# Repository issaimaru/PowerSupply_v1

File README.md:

# アズサ(Azusa)

<br>

<br>
この基板はJLCPCB様のFree PCB Sponsorshipにて制作しています．<br>

## Overview
  [MotorDriver-Controller_v4](https://github.com/TNCT-Mechatech/MotorDriver-Controller_v4)の機能+αと電源回路を合体させた統合型電源基板<br>
 
## Environments
&emsp;
&emsp;&emsp;
<br>

## Usage

1. [DriveUnit Bseries](https://github.com/Issaimaru/MoterDriver_v1)を使用したいチャネルのカードエッジコネクタに差し込む．<br>
1. モータードライバを差し込んだエッジコネクタと同じチャネルにモータを接続し，必要に応じて同じチャネルのコネクタにロータリーエンコーダを接続する．<br>
1. 非常停止スイッチを刺したコネクタの下にあるトグルスイッチをONに，それ以外のトグルスイッチをOFFにする．
1. XT90とUSB Type-Cからそれぞれ電源を供給し，非常停止スイッチをONにすると稼働する．
> **Note**<br>
> USB Type-C用電源を省略する方法はDescriptionsを参照<br>

## Features
<dl>
  <dt>通信プロトコル</dt>
  <dd>CAN with Flexible Data Rate(CAN FD)</dd>
  <dt>通信用コネクタ・ケーブル</dt>
  <dd>RJ-45/LANケーブル</dd>
  <dt>マイクロコンピュータ</dt>
  <dd>STM32F446RE</dd>
  <dt>特殊回路</dt>
  <dd>
  ・オートディスチャージ回路<br>
  ・車載用スローブローヒューズ

  <dt>保護回路(電源側)</dt>
  <dd>
  ・過電流保護(閾値可変)<br>
  ・ヒステリシス付き過熱保護<br>
  ・短絡保護<br>
  ・突入電流抑制<br>
  </dd>
  <dt>保護回路(信号側)</dt>
  <dd>
  ・過電圧保護<br>
  ・過電圧クランプ<br>
  ・突入電流抑制<br>
  ・過電流保護(東芝のeFuseを使用)<br>
  ・過熱保護<br>

## Descriptions
本ハードウェアの使用方法を詳しく書いていきます．<br>
質問や連絡等あれば[@TakenMaker](https://twitter.com/TakenMaker)までお願いします．<br>

### 回路図
&ensp;&ensp;

#### 始動方法
始動方法については[Usage](#usage)で示しました．<br>
ここでは始動時の応用的な使い方について紹介していきます．

- 信号用バッテリーの省略

<br>

JP6で信号用の電源をUSB給電or外部給電に切り替えることができます．<br>
外部電源としては，SPOWのピンに接続された電源かリポバッテリーか選ぶことができます．<br>
リポバッテリーの場合は「GND」と「SPOW」のピンヘッダを短絡してください．<br>
その際にE5VのLEDが点灯していることを確認してください．

## Bills of materials
> **Note**<br>
>最低限の部品のみここに書いています．<br>
>はんだ付けに必要な部品を調べるときは以下のexcelファイルを見るか，BOMファイルを出力してください．<br>
>[アズサ(Azusa)-ver2.0_必要部品.xlsx](src/%E3%82%A2%E3%82%BA%E3%82%B5(Azusa)-ver2.0_%E5%BF%85%E8%A6%81%E9%83%A8%E5%93%81.xlsx)
<br>
<dl>
  <dt>マイクロコンピュータ</dt>
  <dd>

  [STM32F446RET6](https://www.digikey.jp/ja/products/detail/stmicroelectronics/STM32F446RET6/5175962)

  </dd>

  <dt>電流センサ</dt>
  <dd>
  
  [CZ-3A04](https://www.digikey.jp/ja/products/detail/asahi-kasei-microdevices-akm/CZ3A04/11570562)

  </dd>
  <dt>CANトランシーバ</dt>
  <dd>

  [MCP2558FDT-H/MNY](https://www.digikey.jp/ja/products/detail/microchip-technology/MCP2558FDT-H-MNY/6009304)

  </dd>
  <dt>CANコントローラ</dt>
  <dd>

  [MCP2517FDT-H/SL](https://www.digikey.jp/ja/products/detail/microchip-technology/MCP2517FDT-H-SL/7801797)

  </dd>
  <dt>ヒートシンク</dt>
  <dd>
  
  [V2020B](https://www.digikey.jp/ja/products/detail/assmann-wsw-components/V2020B/8826902)
  
  </dd>
  <dt>ヒューズ</dt>
  <dd>

  [0297030.WXT](https://www.digikey.jp/en/products/detail/littelfuse-inc/0297030-WXT/5233697)

  </dd>
  <dt>USB・シリアル変換IC</dt>
  <dd>

  [CH340E](https://akizukidenshi.com/catalog/g/gI-13543/)

  </dd>
  <dt>NTCサーミスタ</dt>
  <dd>

  [NCU15WB473F60RC](https://www.digikey.jp/ja/products/detail/murata-electronics/NCU15WB473F60RC/9686720)

  </dd>
  <dt>DIPスイッチ</dt>
  <dd>

  [RDS-16S-1055-SMT-TR](https://www.digikey.jp/ja/products/detail/cui-devices/RDS-16S-1055-SMT-TR/12424507)

  </dd>
</dl>

## Contact
- Twitter [@TakenMaker](https://twitter.com/TakenMaker)

## Author
    
<table>
  <tr>
    <td align="center"><a href="https://github.com/Issaimaru"><br /></a>Issaimaru</td>
  </tr>
</table>
    
## Licence
  - Copyright © 2022-2023 Issaimaru<br>

本ハードウェアは，Apache License Version 2.0の下で配布されます．<br>
詳しくはLICENSEファイルをご確認ください．<br>

## 回路図のダウンロード(クローン)方法
1. Gitをインストールする．<br>Gitのインストール方法は[ここ](https://www.sejuku.net/blog/73444)を参照．
1. コマンドプロンプトを立ち上げる．
1. `cd ”ダウンロード先フォルダの絶対パス” `<br>
1. `git clone https://github.com/Issaimaru/PowerSupply_v1.git`<br>

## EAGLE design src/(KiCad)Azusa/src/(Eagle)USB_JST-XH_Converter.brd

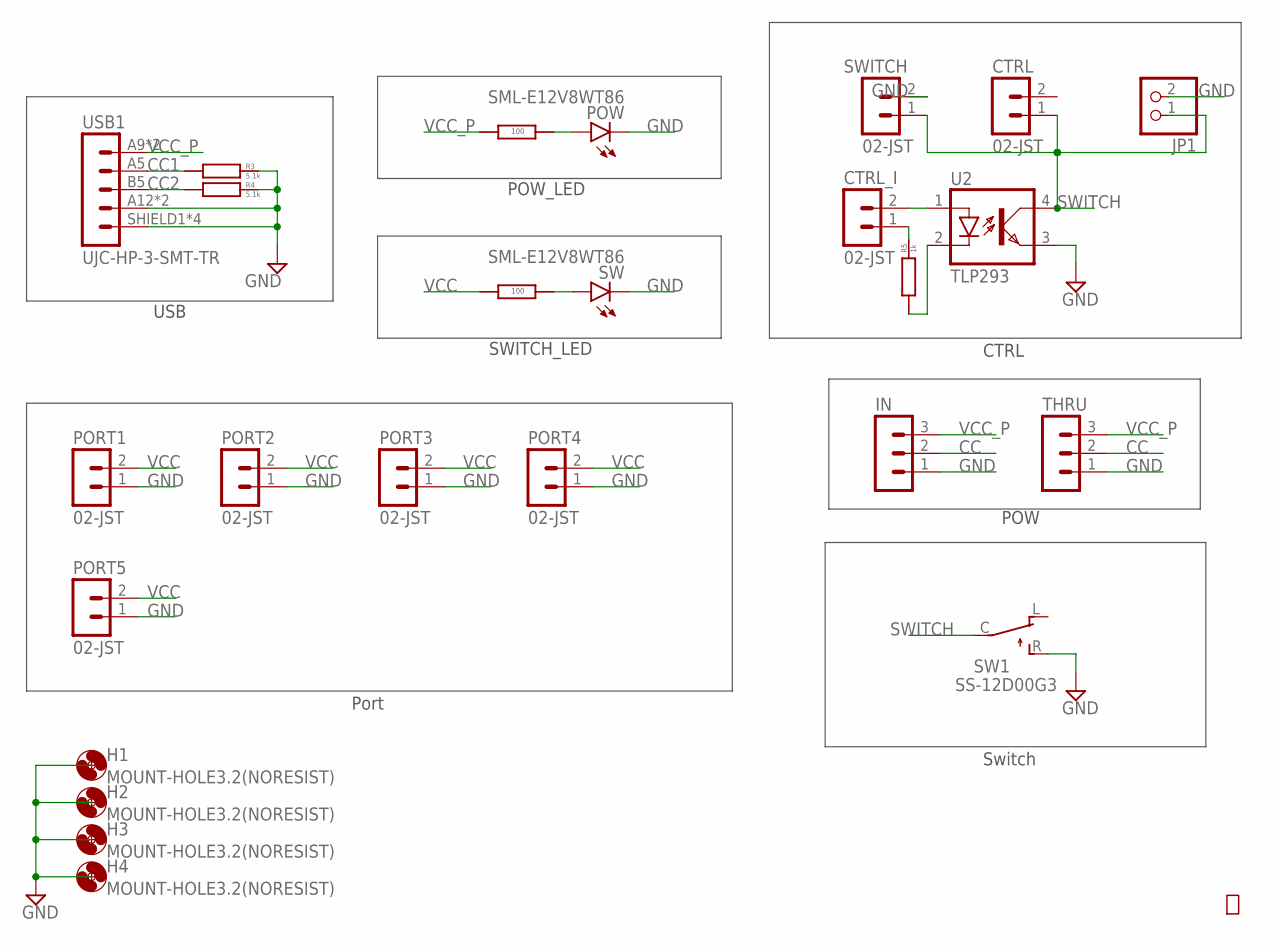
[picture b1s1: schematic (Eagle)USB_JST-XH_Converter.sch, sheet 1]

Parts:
CTRL: 02-JST; B2B-XH
CTRL_I: 02-JST; B2B-XH
H1, H2, H3, H4: MOUNT-HOLE3.2(NORESIST); 3,2
IN: 03-JST; B3B-XH
JP1: PINHD-1X2; 1X02
PORT1, PORT2, PORT3, PORT4, PORT5: 02-JST; B2B-XH
POW: SML-E12V8WT86
R1, R2: RG2012N-101-B-T5; RG2012
R3, R4: 5.1k; RG2012
R5: 1k; RG2012
SW: SML-E12V8WT86
SW1: SS-12D00G3
SWITCH: 02-JST; B2B-XH
THRU: 03-JST; B3B-XH
U2: TLP293; SO4_TOS
USB1: UJC-HP-3-SMT-TR

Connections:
CC: IN.2, THRU.2; also elsewhere on the board
CC1: R3.LEFT, USB1.A5 (CC1); also elsewhere on the board
CC2: R4.LEFT, USB1.B5 (CC2); also elsewhere on the board
GND: H1.P$1, H2.P$1, H3.P$1, H4.P$1, IN.1, JP1.2, PORT1.1, PORT2.1, PORT3.1, PORT4.1, PORT5.1, POW.K (C), R3.RIGHT, R4.RIGHT, SW.K (C), SW1.R, SWITCH.2, THRU.1, U2.3, USB1.A12 (GND), USB1.B12 (GND), USB1.SHIELD1 (SHIELD), USB1.SHIELD2 (SHIELD), USB1.SHIELD3 (SHIELD), USB1.SHIELD4 (SHIELD); also elsewhere on the board
unnamed: POW.A, R1.LEFT
unnamed: R2.LEFT, SW.A
unnamed: CTRL_I.2, U2.1
unnamed: CTRL_I.1, R5.RIGHT
unnamed: R5.LEFT, U2.2
SWITCH: CTRL.1, JP1.1, SW1.C, SWITCH.1, U2.4; also elsewhere on the board
VCC: PORT1.2, PORT2.2, PORT3.2, PORT4.2, PORT5.2, R2.RIGHT; also elsewhere on the board
VCC_P: IN.3, R1.RIGHT, THRU.3, USB1.A9 (V-BUS), USB1.B9 (V-BUS); also elsewhere on the board

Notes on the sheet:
Switch
Port
USB
SWITCH_LED
POW_LED
POW
CTRL

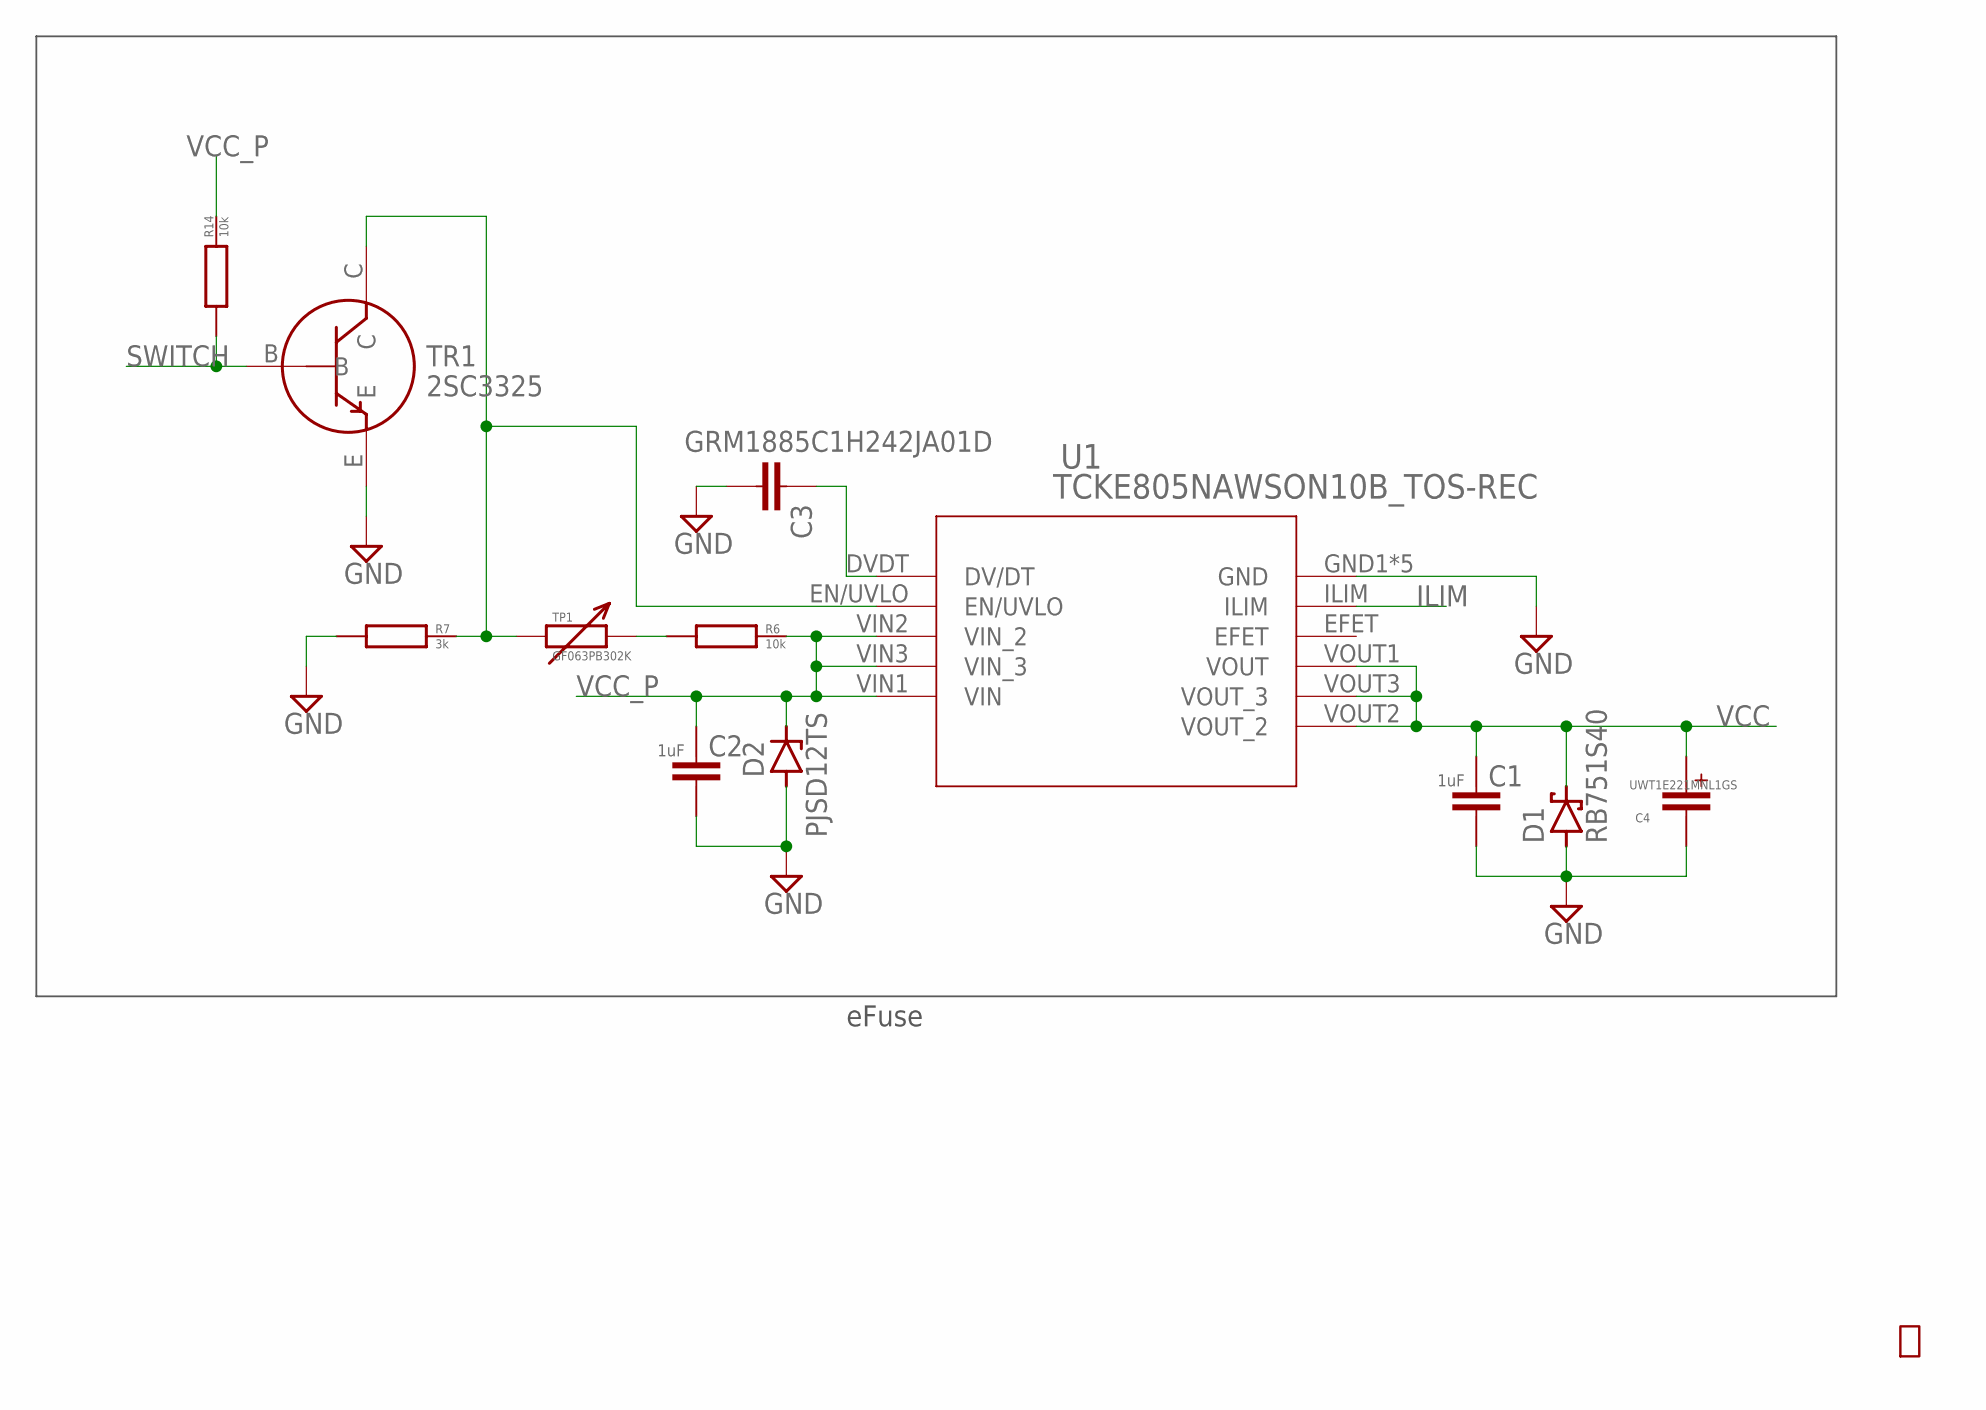
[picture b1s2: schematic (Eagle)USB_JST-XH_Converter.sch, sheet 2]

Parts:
C1, C2: GRM21BC72A105KE01
C3: GRM1885C1H242JA01D; GRM18
C4: UWT1E221MNL1GS
D1: RB751S40; SOD-523
D2: PJSD12TS; SOD-523
R6, R14: 10k; RG2012
R7: 3k; RG2012
TP1: GF063PB302K; GF063PB104K
TR1: 2SC3325
U1: TCKE805NAWSON10B_TOS-REC; WSON10B_TOS-RIC

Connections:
GND: C1.P$2, C2.P$2, C3.R (2), C4.C (CATHODE), D1.A, D2.A, R7.LEFT, TR1.E, U1.GND1 (GND), U1.GND2 (GND), U1.GND3 (GND), U1.GND4 (GND), U1.GND5 (GND); also elsewhere on the board
ILIM: U1.ILIM; also elsewhere on the board
unnamed: R7.RIGHT, TP1.LEFT, TR1.C, U1.EN/UVLO
unnamed: R6.LEFT, TP1.CENTER (RIGHT), TP1.RIGHT
unnamed: C3.L (1), U1.DVDT (DV/DT)
SWITCH: R14.LEFT, TR1.B; also elsewhere on the board
VCC: C1.P$1, C4.A (ANODE), D1.C, U1.VOUT1 (VOUT), U1.VOUT2 (VOUT_2), U1.VOUT3 (VOUT_3); also elsewhere on the board
VCC_P: C2.P$1, D2.C, R6.RIGHT, R14.RIGHT, U1.VIN1 (VIN), U1.VIN2 (VIN_2), U1.VIN3 (VIN_3); also elsewhere on the board

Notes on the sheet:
eFuse

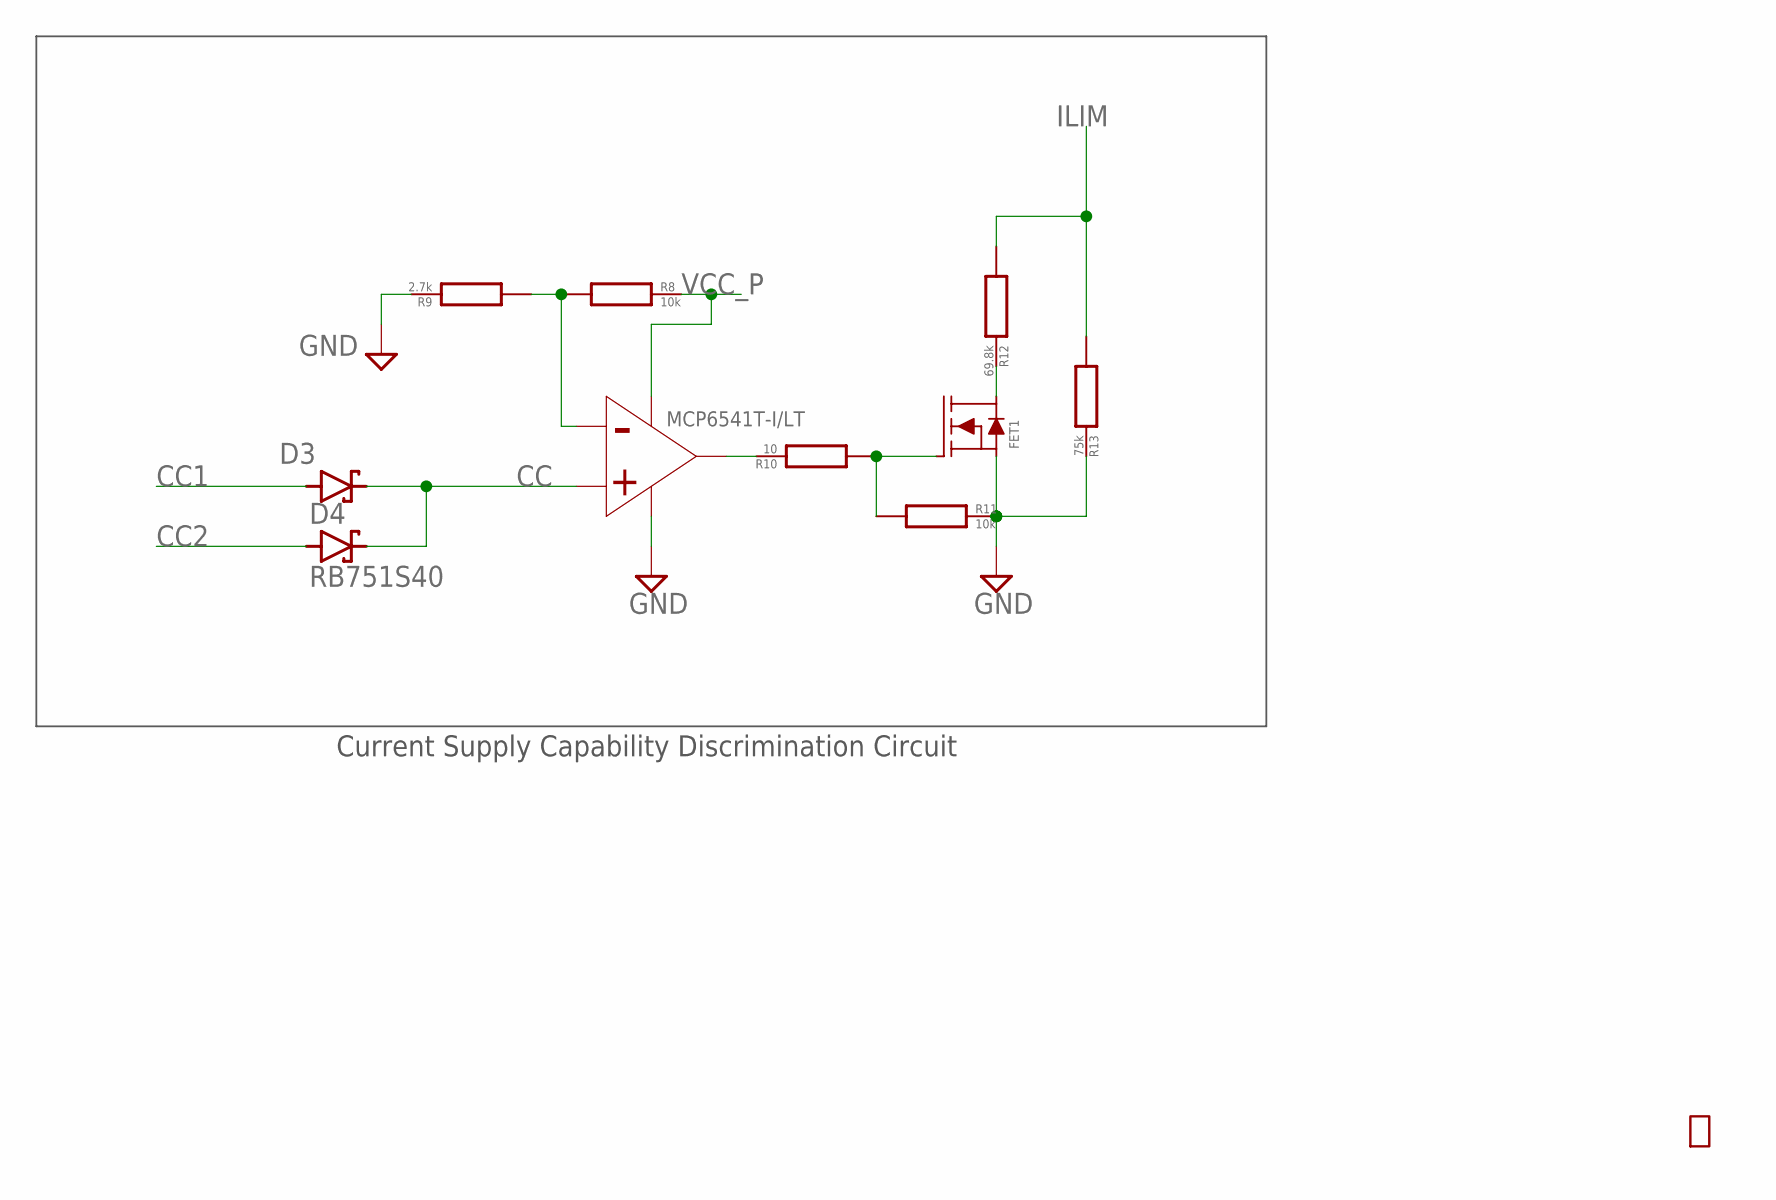
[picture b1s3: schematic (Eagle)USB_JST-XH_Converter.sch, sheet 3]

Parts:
COMP1: MCP6541T-I/LT; SC-70-5
D3, D4: RB751S40; SOD-523
FET1: BSS138; SOT-23
R8, R11: 10k; RG2012
R9: 2.7k; RG2012
R10: 10; RG2012
R12: 69.8k; RG2012
R13: 75k; RG2012

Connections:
CC: COMP1.IN+, D3.C, D4.C; also elsewhere on the board
CC1: D3.A; also elsewhere on the board
CC2: D4.A; also elsewhere on the board
GND: COMP1.VSS, FET1.S, R9.RIGHT, R11.RIGHT, R13.RIGHT; also elsewhere on the board
ILIM: R12.LEFT, R13.LEFT; also elsewhere on the board
unnamed: COMP1.IN-, R8.LEFT, R9.LEFT
unnamed: FET1.G, R10.LEFT, R11.LEFT
unnamed: COMP1.OUT, R10.RIGHT
unnamed: FET1.D, R12.RIGHT
VCC_P: COMP1.VDD, R8.RIGHT; also elsewhere on the board

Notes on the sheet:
Current Supply Capability Discrimination Circuit

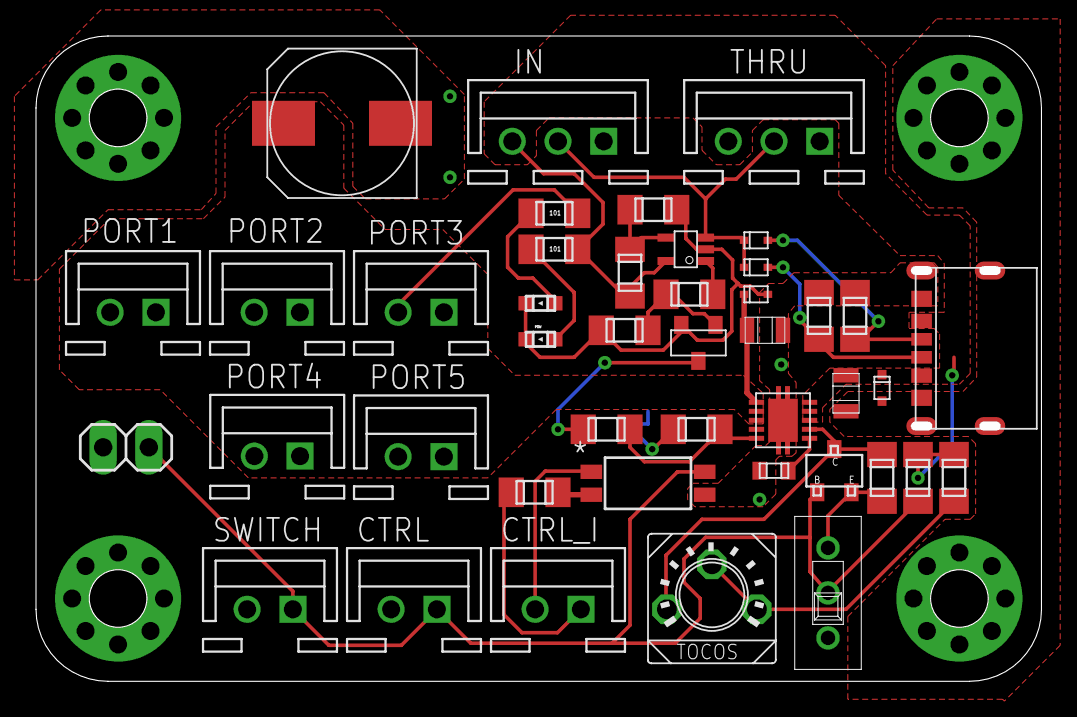
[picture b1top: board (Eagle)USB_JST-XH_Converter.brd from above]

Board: 2 copper layers, 55.9 x 35.9 mm, 47 parts (0 on the bottom side), 20 nets.

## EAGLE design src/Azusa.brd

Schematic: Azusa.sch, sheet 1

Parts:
C2, C47, C50, C53, C56, C66, C67, C69, C71: GRM21BC72A105KE01
C3, C6, C8, C10, C11, C37, C38, C43, C46, C57, C60, C61, C64, C65, C70, C72, C73: GCM188L81H104KA57
C4, C5: GRM32ER71H106KA12
C7: A768EB566M1VLAE042
C9, C12: GRM32ER71E226KE15; 3225M
C39, C40, C41, C42, C44, C45, C48, C49, C51, C52, C54, C55, C58, C59, C62, C63: GRM1885C1H102JA01D; GRM18
C68: GRM0335C1H620GA01D; GRM0335C1E240GA01D
CON1, CON2, CON3, CON4: XT60PW-F
CON5: XT90PW-F
CTRL1, CTRL2: 02-JST; B2B-XH
D1, D2, D4: GS2M-LTP
D3: PJSD12TS; SOD-523
ECHO: PINHD-1X2; 1X02
EDGE1, EDGE2, EDGE3, EDGE4: 10046971-019LF-FEMAL; 10046971-019LF
FUSE1: FUSEHOLDER-3568
GND: PINHD-1X2; 1X02
H1, H2, H3, H4: MOUNT-HOLE3.2(NORESIST); 3,2
IN: XT90PW-M
INV_SW1, INV_SW2: 02-JST; B2B-XH
JP1, JP6, JP8, JP9, JP10: PINHD-1X3; 1X03
L1: 4.7uH; NRS5030T4R7MMGJ
LED1, LED2, LED3, LED8, LED9, LED10, LED11, LED12, LED13, LED14: SML-E12V8WT86
LED4: SMLE13BC8T; SML-E12V8WT86
NTC1: NCU15WB473F60RC
POW: 02-JST; B2B-XH
POW1: PINHD-1X2; 1X02
Q1, Q6, Q10: SQJA16EP-T1_GE3
Q2: SSM3J332R; SOT-23F
Q11, Q12: TMBT3906
R1, R67, R99, R104: 11.8k; CR0603
R2, R5, R79, R113, R116: 1.1k; CR0603
R3: 10; 0411V
R4: 560; CR0603
R6: 820; CR0603
R8, R9: 5.1k; CR0603
R10: 150Ω; CR0603
R12, R20, R21, R60, R65, R71, R115, R119, R121: 10k; CR0603
R18: 12k; CR0603
R19: 3k; CR0603
R22, R61, R66, R72: 20k; CR0603
R23, R24, R33, R58, R59, R62, R63, R64, R68, R69, R70, R73, R77, R120: 1k; CR0603
R32: 10; CR0603
R54, R95, R100, R105: 1.2k; CR0603
R55, R96, R101, R106: 15.8k; CR0603
R56, R97, R102, R107: 1.6k; CR0603
R57, R98, R103, R108: 3.3; CR0603
R74: 0; CR0603
R75: ∞; CR0603
R76: 56k; CR0603
R78, R85, R88: 100; CR0603
R80: 33k; CR0603
R81: 1.8k; CR0603
R82: 100k; CR0603
R83: 187k; CR0603
R84: 0Ω; CR0603
R86, R87, R89: 150; CR0603
R122: 300; CR0603
R123: 270; CR0603
SB1, SB2, SB3, SB4, SB8: RSX101VAM-30TR
SB5: V2P22LHM3/H
SB6: 1SS404,H3F
SW4, SW5: 2MS1-T2-B4-M2-Q-E-S
THRU1, THRU2: 02-JST; B2B-XH
TLP1, TLP3: TLP152
TP1, TP2, TP3, TP4, TP5, TP6, TP7, TP8: GF063PB103K; GF063PB104K
TR3: 2SC3325
U3: CH340E; MSOP-10
U4, U6, U8, U9: CZ-3A04; CZ3A07
U5: AP63205WU-7; AP63203WU-7
U7, U11, U12, U24, U27: MCP6541T-I/LT; SC-70-5
U10, U13, U17, U18, U21, U23, U25: TC7S14F
U14: TCK420G
U15: TCKE805NAWSON10B_TOS-REC; WSON10B_TOS-RIC
U16, U19, U26: TC7SH00FULJ; SSOP5-P-0.65A
U20: TLP293
U$4: AZ1117CH-3.3TRG1; AZ1117C
USB1: 5077CR-16SMC2-BK-TR
ZD1: MMSZ5231B-TP
ZD5: MMBZ5248B-TP

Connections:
5V1: C73.P$1, R121.RIGHT, R123.LEFT, U16.VCC, U17.VCC, U18.VCC, U19.VCC, U21.VCC, ZD1.CATHODE (C)
+3V3: C3.P$2, C11.P$1, C12.L (1), C37.P$2, C38.P$2, C57.P$2, C61.P$2, C72.P$1, EDGE1.P$27 (P27), EDGE2.P$27 (P27), EDGE3.P$27 (P27), EDGE4.P$27 (P27), R1.RIGHT, R21.LEFT, R24.RIGHT, R33.RIGHT, R55.RIGHT, R58.RIGHT, R59.RIGHT, R60.LEFT, R63.RIGHT, R64.RIGHT, R65.LEFT, R67.RIGHT, R69.RIGHT, R70.RIGHT, R71.LEFT, R80.LEFT, R82.LEFT, R88.RIGHT, R96.RIGHT, R99.RIGHT, R101.RIGHT, R104.RIGHT, R106.RIGHT, U3.3V3, U3.VCC, U4.VDD, U6.VDD, U7.VDD, U8.VDD, U9.VDD, U10.VCC, U11.VDD, U12.VDD, U13.VCC, U23.VCC, U24.VDD, U25.VCC, U26.VCC, U27.VDD, U$4.OUTPUT, U$4.VOUT (OUTPUT); also elsewhere on the board
+5V: C9.L (1), C10.P$1, Q2.S (SOURCE), Q11.E, R89.RIGHT, U$4.INPUT; also elsewhere on the board
CS1_OCD1: C44.L (1), JP8.3, R58.LEFT, U4.OCD1
CS1_OCD2: C45.L (1), JP8.1, R59.LEFT, U4.OCD2
CS1_REF1: C41.L (1), R1.LEFT, TP1.CENTER (LEFT), TP1.LEFT, U4.REF1
CS1_REF2: C42.L (1), R55.LEFT, TP2.CENTER (LEFT), TP2.LEFT, U4.REF2
CS2_OCD1: C48.L (1), JP1.3, R24.LEFT, U6.OCD1
CS2_OCD2: C49.L (1), JP1.1, R33.LEFT, U6.OCD2
CS2_REF1: C39.L (1), R67.LEFT, TP3.CENTER (LEFT), TP3.LEFT, U6.REF1
CS2_REF2: C40.L (1), R96.LEFT, TP4.CENTER (LEFT), TP4.LEFT, U6.REF2
CS3_OCD1: C51.L (1), JP9.3, R63.LEFT, U8.OCD1
CS3_OCD2: C52.L (1), JP9.1, R64.LEFT, U8.OCD2
CS3_REF1: C58.L (1), R99.LEFT, TP5.CENTER (LEFT), TP5.LEFT, U8.REF1
CS3_REF2: C59.L (1), R101.LEFT, TP6.CENTER (LEFT), TP6.LEFT, U8.REF2
CS4_OCD1: C54.L (1), JP10.3, R69.LEFT, U9.OCD1
CS4_OCD2: C55.L (1), JP10.1, R70.LEFT, U9.OCD2
CS4_REF1: C62.L (1), R104.LEFT, TP7.CENTER (LEFT), TP7.LEFT, U9.REF1
CS4_REF2: C63.L (1), R106.LEFT, TP8.CENTER (LEFT), TP8.LEFT, U9.REF2
CURRENT1: C43.P$2, R57.LEFT; also elsewhere on the board
CURRENT2: C46.P$2, R98.LEFT; also elsewhere on the board
CURRENT3: C60.P$2, R103.LEFT; also elsewhere on the board
CURRENT4: C64.P$2, R108.LEFT; also elsewhere on the board
DIR1: EDGE1.P$26 (P26); also elsewhere on the board
DIR2: EDGE2.P$26 (P26); also elsewhere on the board
DIR3: EDGE3.P$26 (P26); also elsewhere on the board
DIR4: EDGE4.P$26 (P26); also elsewhere on the board
E5V: C7.ANODE, JP6.3, L1.R, R86.RIGHT, U5.FB
EMERGENCY: R120.RIGHT, U14.VCT, U18.IN (I), U21.OUT (O)
IN1: EDGE1.P$6 (P6), EDGE1.P$7 (P7), EDGE1.P$8 (P8), EDGE1.P$9 (P9), EDGE1.P$10 (P10), EDGE1.P$11 (P11), EDGE1.P$40 (P40), EDGE1.P$41 (P41), EDGE1.P$42 (P42), EDGE1.P$43 (P43), EDGE1.P$44 (P44), U4.IN
IN2: EDGE2.P$6 (P6), EDGE2.P$7 (P7), EDGE2.P$8 (P8), EDGE2.P$9 (P9), EDGE2.P$10 (P10), EDGE2.P$11 (P11), EDGE2.P$40 (P40), EDGE2.P$41 (P41), EDGE2.P$42 (P42), EDGE2.P$43 (P43), EDGE2.P$44 (P44), U6.IN
IN3: EDGE3.P$6 (P6), EDGE3.P$7 (P7), EDGE3.P$8 (P8), EDGE3.P$9 (P9), EDGE3.P$10 (P10), EDGE3.P$11 (P11), EDGE3.P$40 (P40), EDGE3.P$41 (P41), EDGE3.P$42 (P42), EDGE3.P$43 (P43), EDGE3.P$44 (P44), U8.IN
IN4: EDGE4.P$6 (P6), EDGE4.P$7 (P7), EDGE4.P$8 (P8), EDGE4.P$9 (P9), EDGE4.P$10 (P10), EDGE4.P$11 (P11), EDGE4.P$40 (P40), EDGE4.P$41 (P41), EDGE4.P$42 (P42), EDGE4.P$43 (P43), EDGE4.P$44 (P44), U9.IN
IP1: CON1.-, U4.IP
IP2: CON2.-, U6.IP
IP3: CON3.-, U8.IP
IP4: CON4.-, U9.IP
unnamed: R57.RIGHT, U4.VOUT
unnamed: R56.RIGHT, TP2.RIGHT
unnamed: LED2.A, R5.RIGHT
unnamed: CON1.+, EDGE1.P$1 (P1), EDGE1.P$2 (P2), EDGE1.P$3 (P3), EDGE1.P$4 (P4), EDGE1.P$5 (P5), EDGE1.P$45 (P45), EDGE1.P$46 (P46), EDGE1.P$47 (P47), EDGE1.P$48 (P48), EDGE1.P$49 (P49), EDGE1.P$50 (P50)
unnamed: CON2.+, EDGE2.P$1 (P1), EDGE2.P$2 (P2), EDGE2.P$3 (P3), EDGE2.P$4 (P4), EDGE2.P$5 (P5), EDGE2.P$45 (P45), EDGE2.P$46 (P46), EDGE2.P$47 (P47), EDGE2.P$48 (P48), EDGE2.P$49 (P49), EDGE2.P$50 (P50)
unnamed: CON3.+, EDGE3.P$1 (P1), EDGE3.P$2 (P2), EDGE3.P$3 (P3), EDGE3.P$4 (P4), EDGE3.P$5 (P5), EDGE3.P$45 (P45), EDGE3.P$46 (P46), EDGE3.P$47 (P47), EDGE3.P$48 (P48), EDGE3.P$49 (P49), EDGE3.P$50 (P50)
unnamed: LED8.A, R116.RIGHT
unnamed: R74.LEFT, R75.RIGHT, U15.EN/UVLO
unnamed: JP8.2, U10.IN (I)
unnamed: CON4.+, EDGE4.P$1 (P1), EDGE4.P$2 (P2), EDGE4.P$3 (P3), EDGE4.P$4 (P4), EDGE4.P$5 (P5), EDGE4.P$45 (P45), EDGE4.P$46 (P46), EDGE4.P$47 (P47), EDGE4.P$48 (P48), EDGE4.P$49 (P49), EDGE4.P$50 (P50)
unnamed: Q10.D, R3.1
unnamed: R77.LEFT, TLP1.VO (VOUT)
unnamed: R54.RIGHT, TP1.RIGHT
unnamed: R77.RIGHT, R115.RIGHT, TR3.B
unnamed: LED8.K (C), TR3.C, U20.CATHODE
unnamed: LED1.A, R2.RIGHT
unnamed: R60.RIGHT, R61.LEFT, U11.IN-
unnamed: INV_SW1.2, INV_SW2.1, SW4.O, SW5.P
unnamed: C67.P$1, D3.C, JP6.2, R74.RIGHT, U15.VIN1 (VIN), U15.VIN2 (VIN_2), U15.VIN3 (VIN_3)
unnamed: CTRL1.1, CTRL2.1, INV_SW1.1, LED3.K (C), R115.LEFT, SW4.P, THRU1.1, THRU2.1, TR3.E
unnamed: U16.INB (I1), U17.OUT (O)
unnamed: LED3.A, R113.RIGHT
unnamed: FUSE1.R1 (R), FUSE1.R2 (R), IN.+, R79.LEFT
unnamed: Q1.G, Q6.G, U14.VGATE2
unnamed: R8.RIGHT, USB1.CC2
unnamed: R9.RIGHT, USB1.CC1
unnamed: U3.UD+, USB1.DP1, USB1.DP2
unnamed: U3.UD-, USB1.DN1, USB1.DN2
unnamed: R10.RIGHT, U3.TNOW
unnamed: LED4.A, R10.LEFT
unnamed: D1.A, POW1.2
unnamed: R18.LEFT, R19.RIGHT, U5.EN
unnamed: D2.A, POW.2
unnamed: C6.P$2, L1.L, U5.SW
unnamed: C6.P$1, U5.BST
unnamed: R21.RIGHT, R22.LEFT, U7.IN-
unnamed: Q11.B, Q12.B, Q12.C, R12.RIGHT
unnamed: LED12.A, R87.LEFT
unnamed: C69.P$1, Q2.D (DRAIN), Q12.E, SB6.C, U15.VOUT1 (VOUT), U15.VOUT2 (VOUT_2), U15.VOUT3 (VOUT_3)
unnamed: C50.P$1, R62.LEFT, U11.IN+
unnamed: SB2.A, U11.OUT
unnamed: C47.P$1, R23.LEFT, U7.IN+
unnamed: R95.RIGHT, TP3.RIGHT
unnamed: R97.RIGHT, TP4.RIGHT
unnamed: R98.RIGHT, U6.VOUT
unnamed: R100.RIGHT, TP5.RIGHT
unnamed: JP1.2, U23.IN (I)
unnamed: R65.RIGHT, R66.LEFT, U12.IN-
unnamed: C53.P$1, R68.LEFT, U12.IN+
unnamed: SB3.A, U12.OUT
unnamed: JP9.2, U13.IN (I)
unnamed: R68.RIGHT, U13.OUT (O)
unnamed: R71.RIGHT, R72.LEFT, U24.IN-
unnamed: C56.P$1, R73.LEFT, U24.IN+
unnamed: SB4.A, U24.OUT
unnamed: R78.LEFT, U26.OUT (O)
unnamed: C71.P$1, R120.LEFT, U17.IN (I)
unnamed: R4.RIGHT, U20.ANODE
unnamed: D4.C, R6.LEFT, TLP3.VO (VOUT)
unnamed: Q10.G, R6.RIGHT, R32.RIGHT, R119.RIGHT, ZD5.CATHODE (C)
unnamed: SB1.A, U7.OUT
unnamed: R102.RIGHT, TP6.RIGHT
unnamed: R103.RIGHT, U8.VOUT
unnamed: R105.RIGHT, TP7.RIGHT
unnamed: R107.RIGHT, TP8.RIGHT
unnamed: R108.RIGHT, U9.VOUT
unnamed: Q2.G (GATE), Q11.C, R20.RIGHT
unnamed: R23.RIGHT, U10.OUT (O)
unnamed: R122.LEFT, U19.OUT (O)
unnamed: U16.INA (I0), U18.OUT (O)
unnamed: U16.OUT (O), U19.INA (I0), U19.INB (I1)
unnamed: R121.LEFT, U20.COLLECTOR, U21.IN (I)
unnamed: R122.RIGHT, TLP3.ANODE
unnamed: C66.P$1, EDGE1.P$12 (P12), EDGE1.P$13 (P13), EDGE1.P$14 (P14), EDGE1.P$15 (P15), EDGE1.P$16 (P16), EDGE1.P$17 (P17), EDGE1.P$18 (P18), EDGE1.P$19 (P19), EDGE1.P$20 (P20), EDGE1.P$21 (P21), EDGE1.P$22 (P22), EDGE1.P$23 (P23), EDGE2.P$12 (P12), EDGE2.P$13 (P13), EDGE2.P$14 (P14), EDGE2.P$15 (P15), EDGE2.P$16 (P16), EDGE2.P$17 (P17), EDGE2.P$18 (P18), EDGE2.P$19 (P19), EDGE2.P$20 (P20), EDGE2.P$21 (P21), EDGE2.P$22 (P22), EDGE2.P$23 (P23), EDGE3.P$12 (P12), EDGE3.P$13 (P13), EDGE3.P$14 (P14), EDGE3.P$15 (P15), EDGE3.P$16 (P16), EDGE3.P$17 (P17), EDGE3.P$18 (P18), EDGE3.P$19 (P19), EDGE3.P$20 (P20), EDGE3.P$21 (P21), EDGE3.P$22 (P22), EDGE3.P$23 (P23), EDGE4.P$12 (P12), EDGE4.P$13 (P13), EDGE4.P$14 (P14), EDGE4.P$15 (P15), EDGE4.P$16 (P16), EDGE4.P$17 (P17), EDGE4.P$18 (P18), EDGE4.P$19 (P19), EDGE4.P$20 (P20), EDGE4.P$21 (P21), EDGE4.P$22 (P22), EDGE4.P$23 (P23), Q1.S1 (S), Q1.S2 (S), Q1.S3 (S), Q6.S1 (S), Q6.S2 (S), Q6.S3 (S), R3.2, R5.LEFT, SB5.A, U14.VOUT
unnamed: D4.A, R32.LEFT
unnamed: R62.RIGHT, U23.OUT (O)
unnamed: JP10.2, U25.IN (I)
unnamed: R73.RIGHT, U25.OUT (O)
unnamed: R76.RIGHT, U15.ILIM
unnamed: C68.1, U15.DVDT (DV/DT)
unnamed: R78.RIGHT, TLP1.ANODE
unnamed: LED9.A, R79.RIGHT
unnamed: R84.RIGHT, U3.RTS#
unnamed: R80.RIGHT, R81.LEFT, R83.LEFT, U27.IN+
unnamed: R84.LEFT, U3.CTS#
unnamed: LED10.A, R85.RIGHT
unnamed: LED11.A, R86.LEFT
unnamed: R83.RIGHT, R85.LEFT, SB8.A, U27.OUT
unnamed: LED13.A, R89.LEFT
unnamed: LED14.A, R88.LEFT
PGND: C2.P$2, C65.P$2, C66.P$2, C70.P$2, C71.P$2, C73.P$2, CON5.-, EDGE1.P$28 (P28), EDGE1.P$29 (P29), EDGE1.P$30 (P30), EDGE1.P$31 (P31), EDGE1.P$32 (P32), EDGE1.P$33 (P33), EDGE1.P$34 (P34), EDGE1.P$35 (P35), EDGE1.P$36 (P36), EDGE1.P$37 (P37), EDGE1.P$38 (P38), EDGE1.P$39 (P39), EDGE2.P$28 (P28), EDGE2.P$29 (P29), EDGE2.P$30 (P30), EDGE2.P$31 (P31), EDGE2.P$32 (P32), EDGE2.P$33 (P33), EDGE2.P$34 (P34), EDGE2.P$35 (P35), EDGE2.P$36 (P36), EDGE2.P$37 (P37), EDGE2.P$38 (P38), EDGE2.P$39 (P39), EDGE3.P$28 (P28), EDGE3.P$29 (P29), EDGE3.P$30 (P30), EDGE3.P$31 (P31), EDGE3.P$32 (P32), EDGE3.P$33 (P33), EDGE3.P$34 (P34), EDGE3.P$35 (P35), EDGE3.P$36 (P36), EDGE3.P$37 (P37), EDGE3.P$38 (P38), EDGE3.P$39 (P39), EDGE4.P$28 (P28), EDGE4.P$29 (P29), EDGE4.P$30 (P30), EDGE4.P$31 (P31), EDGE4.P$32 (P32), EDGE4.P$33 (P33), EDGE4.P$34 (P34), EDGE4.P$35 (P35), EDGE4.P$36 (P36), EDGE4.P$37 (P37), EDGE4.P$38 (P38), EDGE4.P$39 (P39), GND.2, H1.P$1, H2.P$1, IN.-, INV_SW2.2, LED1.K (C), LED2.K (C), LED9.K (C), Q10.S1 (S), Q10.S2 (S), Q10.S3 (S), R119.LEFT, SW5.O, TLP1.GND, TLP3.CATHODE, TLP3.GND, U14.GND, U16.GND, U17.GND, U18.GND, U19.GND, U20.EMITTER, U21.GND, ZD1.ANODE (A), ZD5.ANODE (A)
PWM1: EDGE1.P$25 (P25); also elsewhere on the board
PWM2: EDGE2.P$25 (P25); also elsewhere on the board
PWM3: EDGE3.P$25 (P25); also elsewhere on the board
PWM4: EDGE4.P$25 (P25); also elsewhere on the board
SGND: C3.P$1, C4.R, C5.R, C7.CATHODE, C8.P$2, C9.R (2), C10.P$2, C11.P$2, C12.R (2), C37.P$1, C38.P$1, C39.R (2), C40.R (2), C41.R (2), C42.R (2), C43.P$1, C44.R (2), C45.R (2), C46.P$1, C47.P$2, C48.R (2), C49.R (2), C50.P$2, C51.R (2), C52.R (2), C53.P$2, C54.R (2), C55.R (2), C56.P$2, C57.P$1, C58.R (2), C59.R (2), C60.P$1, C61.P$1, C62.R (2), C63.R (2), C64.P$1, C67.P$2, C68.2, C69.P$2, C72.P$2, D3.A, EDGE1.P$24 (P24), EDGE2.P$24 (P24), EDGE3.P$24 (P24), EDGE4.P$24 (P24), GND.1, H3.P$1, H4.P$1, LED4.K (C), LED10.K (C), LED11.K (C), LED12.K (C), LED13.K (C), LED14.K (C), NTC1.L (1), POW.1, R8.LEFT, R9.LEFT, R12.LEFT, R19.LEFT, R20.LEFT, R22.RIGHT, R54.LEFT, R56.LEFT, R61.RIGHT, R66.RIGHT, R72.RIGHT, R75.LEFT, R76.LEFT, R81.RIGHT, R95.LEFT, R97.LEFT, R100.LEFT, R102.LEFT, R105.LEFT, R107.LEFT, SB6.A, TLP1.CATHODE, U3.GND, U4.VSS1, U4.VSS2, U5.GND, U6.VSS1, U6.VSS2, U7.VSS, U8.VSS1, U8.VSS2, U9.VSS1, U9.VSS2, U10.GND, U11.VSS, U12.VSS, U13.GND, U15.GND1 (GND), U15.GND2 (GND), U15.GND3 (GND), U15.GND4 (GND), U15.GND5 (GND), U23.GND, U24.VSS, U25.GND, U26.GND, U27.VSS, U$4.GND, USB1.GND1 (GND), USB1.GND2 (GND), USB1.SHIELD1 (SHIELD), USB1.SHIELD2 (SHIELD), USB1.SHIELD3 (SHIELD), USB1.SHIELD4 (SHIELD); also elsewhere on the board
SHUTDOWN: SB1.C, SB2.C, SB3.C, SB4.C, SB8.C, U26.INA (I0), U26.INB (I1); also elsewhere on the board
THERMAL: NTC1.R (2), R82.RIGHT, U27.IN-; also elsewhere on the board
U5V: JP6.1, R87.RIGHT, USB1.VBUS1 (VBUS), USB1.VBUS2 (VBUS)
USART_RX: ECHO.1, U3.TXD; also elsewhere on the board
USART_TX: ECHO.2, U3.RXD; also elsewhere on the board
V+: C4.L, C5.L, C8.P$1, D1.C, D2.C, R18.RIGHT, U5.VIN
VCC: C2.P$1, C65.P$1, C70.P$1, CON5.+, CTRL1.2, CTRL2.2, FUSE1.L1 (L), FUSE1.L2 (L), POW1.1, Q1.D, Q6.D, R2.LEFT, R4.LEFT, R113.LEFT, R116.LEFT, R123.RIGHT, SB5.C, THRU1.2, THRU2.2, TLP1.VCC, TLP3.VCC, U14.VIN

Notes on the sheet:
Battery
Control
Output
DeadTime:0.606ms(approximately)
OCD TIMER
Current Sensor
USB2.0(Type C)
Power Management
GND_COM
OTP
23.368℃/W
Continuous Max:92[A]

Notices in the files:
parts and their libraries:
COPYRIGHT: Copyright (C) 2022 Ultra Librarian. All rights reserved.
